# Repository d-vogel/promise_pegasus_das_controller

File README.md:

# Promise Pegasus DAS controller

The Promise Pegasus DAS is a thuderbolt 2 DAS enclosure.
| Front | Back |
|:-:|:-:|
|||

The goal here is to reverse engineer the backplane and replace the RAID controller with a SATA breakout board and microcontroller.

# Current Status
## reverse engineering
The reverse engineering of the backplane is done, for now described in [docs/backplane.md](docs/backplane.md).

## v0
The first PCB version is not present on the repo. The pinout for both the PCI connector and the ATX24 connector was completely wrong.
Is seems in the debugging process I damaged the CPLD controlling the LEDs, which is why v2 will add a ws2812 control pin.

## v1

This is the current version on the PCB. Pinouts are correct: 
- ✅ the pico is always on
- ✅ the front panel interfaces to the pico
- ✅ pico triggers the PSU
- ✅ CPLD control pins arrive where they should
- ✅ Disk power enable pins work
- ✅ sata works (tested with HDD1 only)
- ❌ ground fill missing, bodge wires were needed.

## v2 (TODO)
- add ws2812 control pin to pico
- add ground fill to the PCB
- add onboard temperature sensor

## v3 eInk front panel?
[waveshare 2.9 inch E-paper Module](https://www.waveshare.com/2.9inch-e-paper-module.htm)

# BOM:
- SATA: https://www.mouser.ch/ProductDetail/Adam-Tech/SATA-A-PL-VT-K-1
- PCI: https://www.mouser.ch/ProductDetail/Amphenol-FCI/10018783-10212TLF
- ATX24pin: https://www.mouser.fr/ProductDetail/TE-Connectivity/1-1775099-3?qs=28ld6GkVMjRzvehyCXdQkg%3D%3D

pio simulator: https://ice458.github.io/tools/pio_sim/index.html

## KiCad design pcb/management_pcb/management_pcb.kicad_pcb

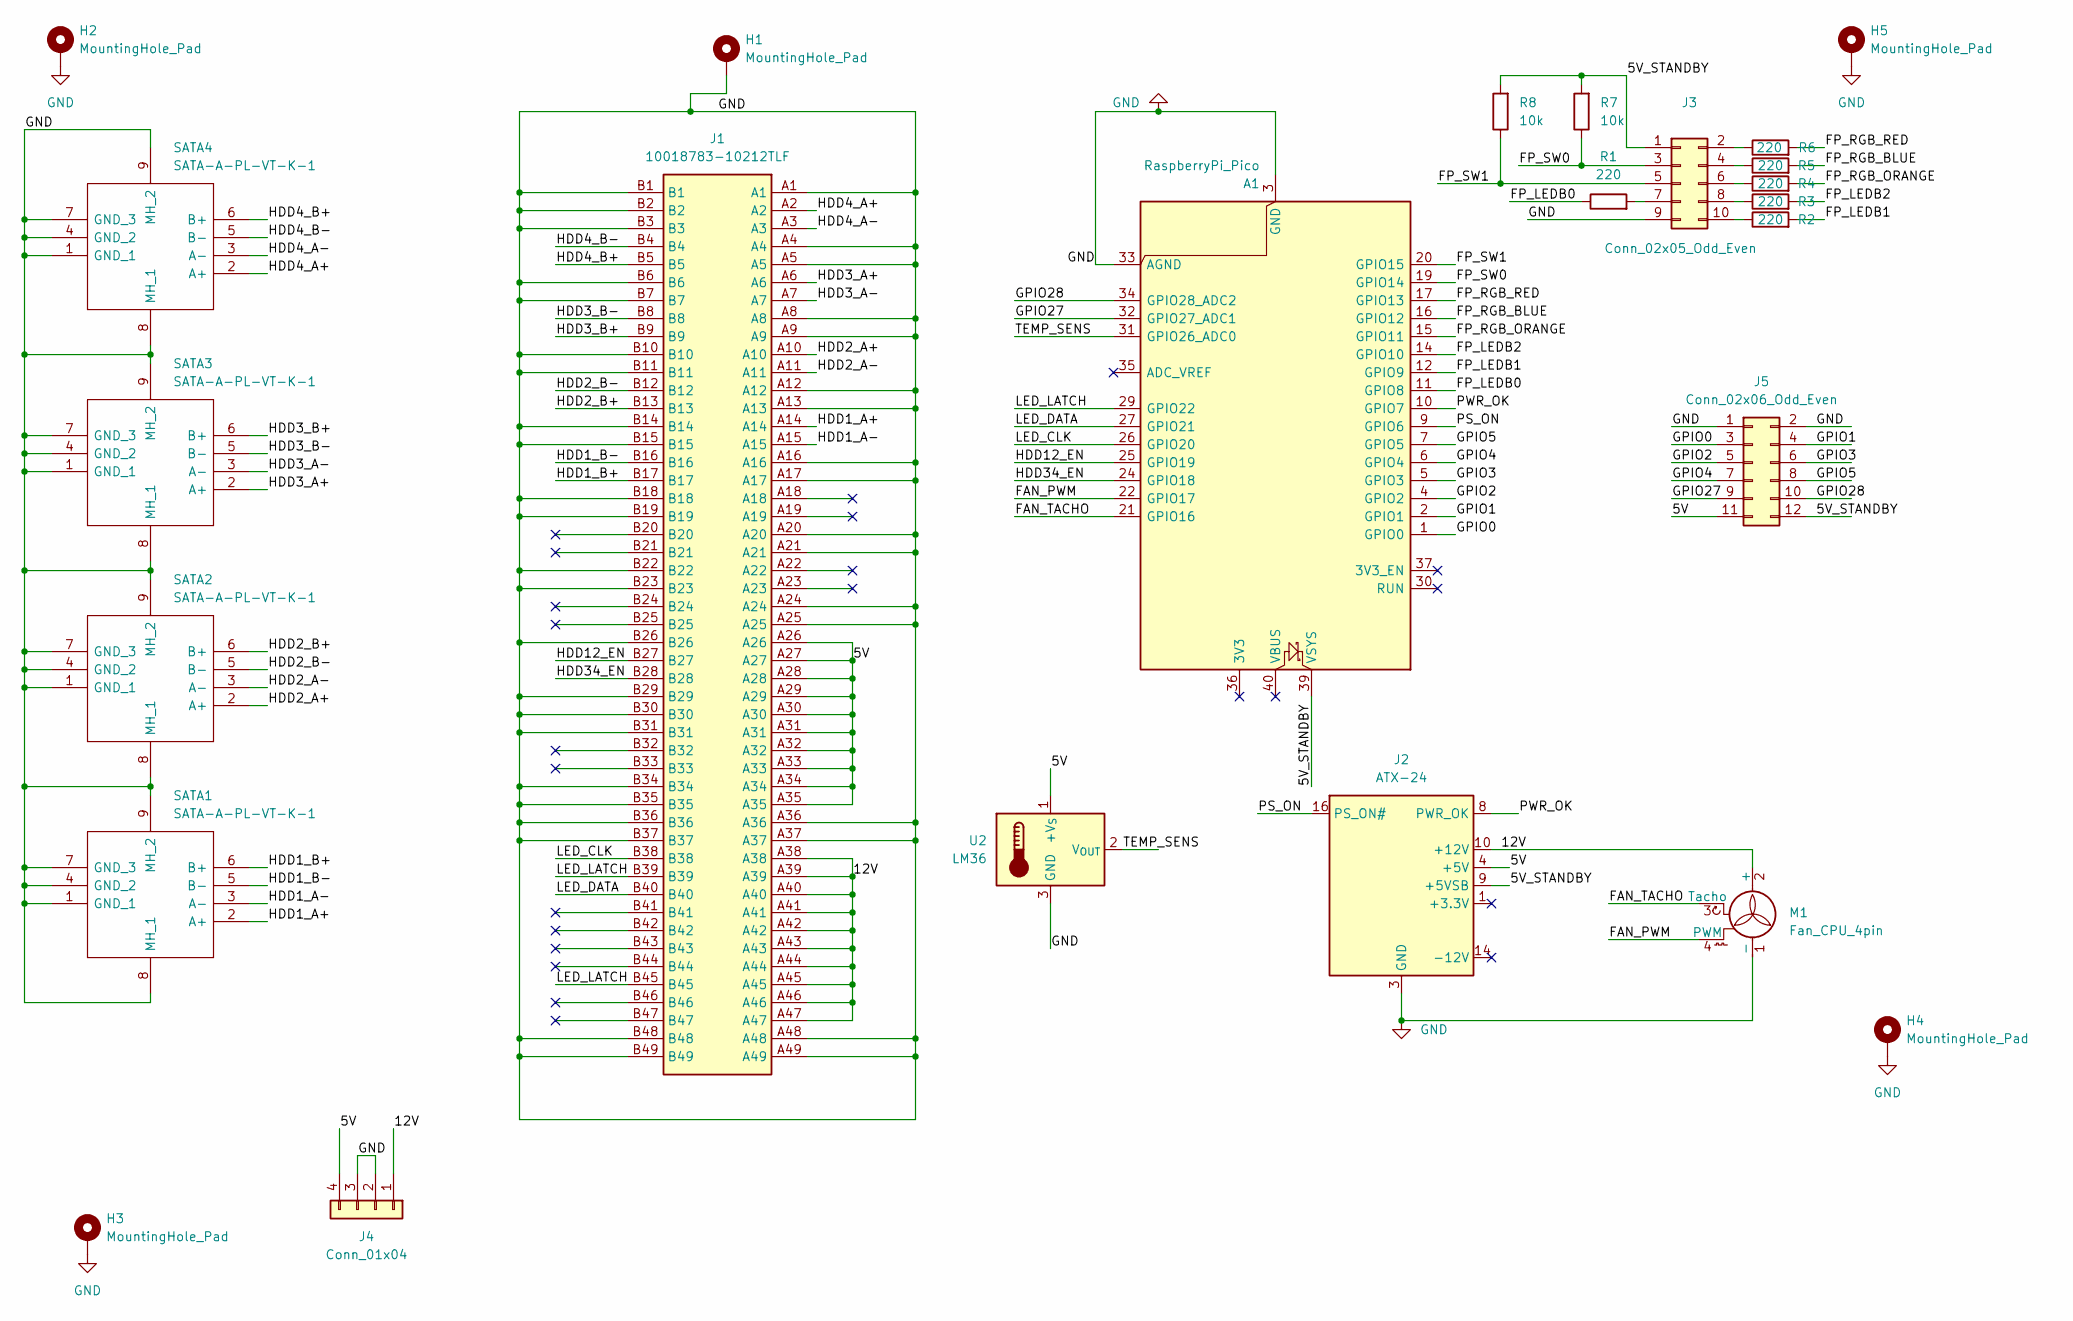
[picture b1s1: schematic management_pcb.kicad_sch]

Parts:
A1: RaspberryPi_Pico; RaspberryPi_Pico_Common_Unspecified
H1, H2, H3, H4, H5: MountingHole_Pad; MountingHole_4.3mm_M4_DIN965_Pad_TopBottom
J1: 10018783-10212TLF; 1001878310212TLF; Mouser Part Number 649-118783-10212TLF
J2: ATX-24; Molex_Mini-Fit_Jr_5566-24A_2x12_P4.20mm_Vertical
J3: Conn_02x05_Odd_Even; IDC_2x05_P2.00mm_Header
J4: Conn_01x04; SolderWire-0.75sqmm_1x04_P7mm_D1.25mm_OD3.5mm
J5: Conn_02x06_Odd_Even; PinHeader_2x06_P2.54mm_Vertical
M1: Fan_CPU_4pin; FanPinHeader_1x04_P2.54mm_Vertical
R1, R2, R3, R4, R5, R6: 220; R_0805_2012Metric
R7, R8: 10k; R_0805_2012Metric
SATA1, SATA2, SATA3, SATA4: SATA-A-PL-VT-K-1; SATAAPLVTK1; Manufacturer_Part_Number SATA-A-PL-VT-K-1
U2: LM36; TO-92_Inline

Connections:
/5V: J1.A26, J1.A27, J1.A28, J1.A29, J1.A30, J1.A31, J1.A32, J1.A33, J1.A34, J1.A35, J2.4 (+5V), J2.6 (+5V), J2.21 (+5V), J2.22 (+5V), J2.23 (+5V), J4.4, J5.11, U2.1 (+V_{S})
/5V_STANDBY: A1.39 (VSYS), J2.9 (+5VSB), J3.1, J5.12, R7.2, R8.2
/12V: J1.A38, J1.A39, J1.A40, J1.A41, J1.A42, J1.A43, J1.A44, J1.A45, J1.A46, J1.A47, J2.10 (+12V), J2.11 (+12V), J4.1, M1.2 (+)
/FAN_PWM: A1.22 (GPIO17), M1.4 (PWM)
/FAN_TACHO: A1.21 (GPIO16), M1.3 (Tacho)
/FP_LEDB0: A1.11 (GPIO8), R1.1
/FP_LEDB1: A1.12 (GPIO9), R2.2
/FP_LEDB2: A1.14 (GPIO10), R3.2
/FP_RGB_BLUE: A1.16 (GPIO12), R5.2
/FP_RGB_ORANGE: A1.15 (GPIO11), R4.2
/FP_RGB_RED: A1.17 (GPIO13), R6.2
/FP_SW0: A1.19 (GPIO14), J3.3, R7.1
/FP_SW1: A1.20 (GPIO15), J3.5, R8.1
/GPIO0: A1.1 (GPIO0), J5.3
/GPIO1: A1.2 (GPIO1), J5.4
/GPIO2: A1.4 (GPIO2), J5.5
/GPIO3: A1.5 (GPIO3), J5.6
/GPIO4: A1.6 (GPIO4), J5.7
/GPIO5: A1.7 (GPIO5), J5.8
/GPIO27: A1.32 (GPIO27_ADC1), J5.9
/GPIO28: A1.34 (GPIO28_ADC2), J5.10
/HDD1_A+: J1.A14, SATA1.2 (A+)
/HDD1_A-: J1.A15, SATA1.3 (A-)
/HDD1_B+: J1.B17, SATA1.6 (B+)
/HDD1_B-: J1.B16, SATA1.5 (B-)
/HDD2_A+: J1.A10, SATA2.2 (A+)
/HDD2_A-: J1.A11, SATA2.3 (A-)
/HDD2_B+: J1.B13, SATA2.6 (B+)
/HDD2_B-: J1.B12, SATA2.5 (B-)
/HDD3_A+: J1.A6, SATA3.2 (A+)
/HDD3_A-: J1.A7, SATA3.3 (A-)
/HDD3_B+: J1.B9, SATA3.6 (B+)
/HDD3_B-: J1.B8, SATA3.5 (B-)
/HDD4_A+: J1.A2, SATA4.2 (A+)
/HDD4_A-: J1.A3, SATA4.3 (A-)
/HDD4_B+: J1.B5, SATA4.6 (B+)
/HDD4_B-: J1.B4, SATA4.5 (B-)
/HDD12_EN: A1.25 (GPIO19), J1.B27
/HDD34_EN: A1.24 (GPIO18), J1.B28
/LED_CLK: A1.26 (GPIO20), J1.B38
/LED_DATA: A1.27 (GPIO21), J1.B40
/LED_LATCH: A1.29 (GPIO22), J1.B39, J1.B45
/PS_ON: A1.9 (GPIO6), J2.16 (PS_ON#)
/PWR_OK: A1.10 (GPIO7), J2.8 (PWR_OK)
/TEMP_SENS: A1.31 (GPIO26_ADC0), U2.2 (V_{OUT})
GND: A1.3 (GND), A1.8 (GND), A1.13 (GND), A1.18 (GND), A1.23 (GND), A1.28 (GND), A1.33 (AGND), A1.38 (GND), H1.1 (1_1), H2.1 (1_1), H3.1 (1_1), H4.1 (1_1), H5.1 (1_1), J1.A1, J1.A4, J1.A5, J1.A8, J1.A9, J1.A12, J1.A13, J1.A16, J1.A17, J1.A20, J1.A21, J1.A24, J1.A25, J1.A36, J1.A37, J1.A48, J1.A49, J1.B1, J1.B2, J1.B3, J1.B6, J1.B7, J1.B10, J1.B11, J1.B14, J1.B15, J1.B18, J1.B19, J1.B22, J1.B23, J1.B26, J1.B29, J1.B30, J1.B31, J1.B34, J1.B35, J1.B36, J1.B37, J1.B48, J1.B49, J2.3 (GND), J2.5 (GND), J2.7 (GND), J2.15 (GND), J2.17 (GND), J2.18 (GND), J2.19 (GND), J2.24 (GND), J3.9, J4.2, J4.3, J5.1, J5.2, M1.1 (-), SATA1.1 (GND_1), SATA1.4 (GND_2), SATA1.7 (GND_3), SATA1.8 (MH_1), SATA1.9 (MH_2), SATA2.1 (GND_1), SATA2.4 (GND_2), SATA2.7 (GND_3), SATA2.8 (MH_1), SATA2.9 (MH_2), SATA3.1 (GND_1), SATA3.4 (GND_2), SATA3.7 (GND_3), SATA3.8 (MH_1), SATA3.9 (MH_2), SATA4.1 (GND_1), SATA4.4 (GND_2), SATA4.7 (GND_3), SATA4.8 (MH_1), SATA4.9 (MH_2), U2.3 (GND)
unnamed: J3.2, R6.1
unnamed: J3.4, R5.1
unnamed: J3.6, R4.1
unnamed: J3.7, R1.2
unnamed: J3.8, R3.1
unnamed: J3.10, R2.1

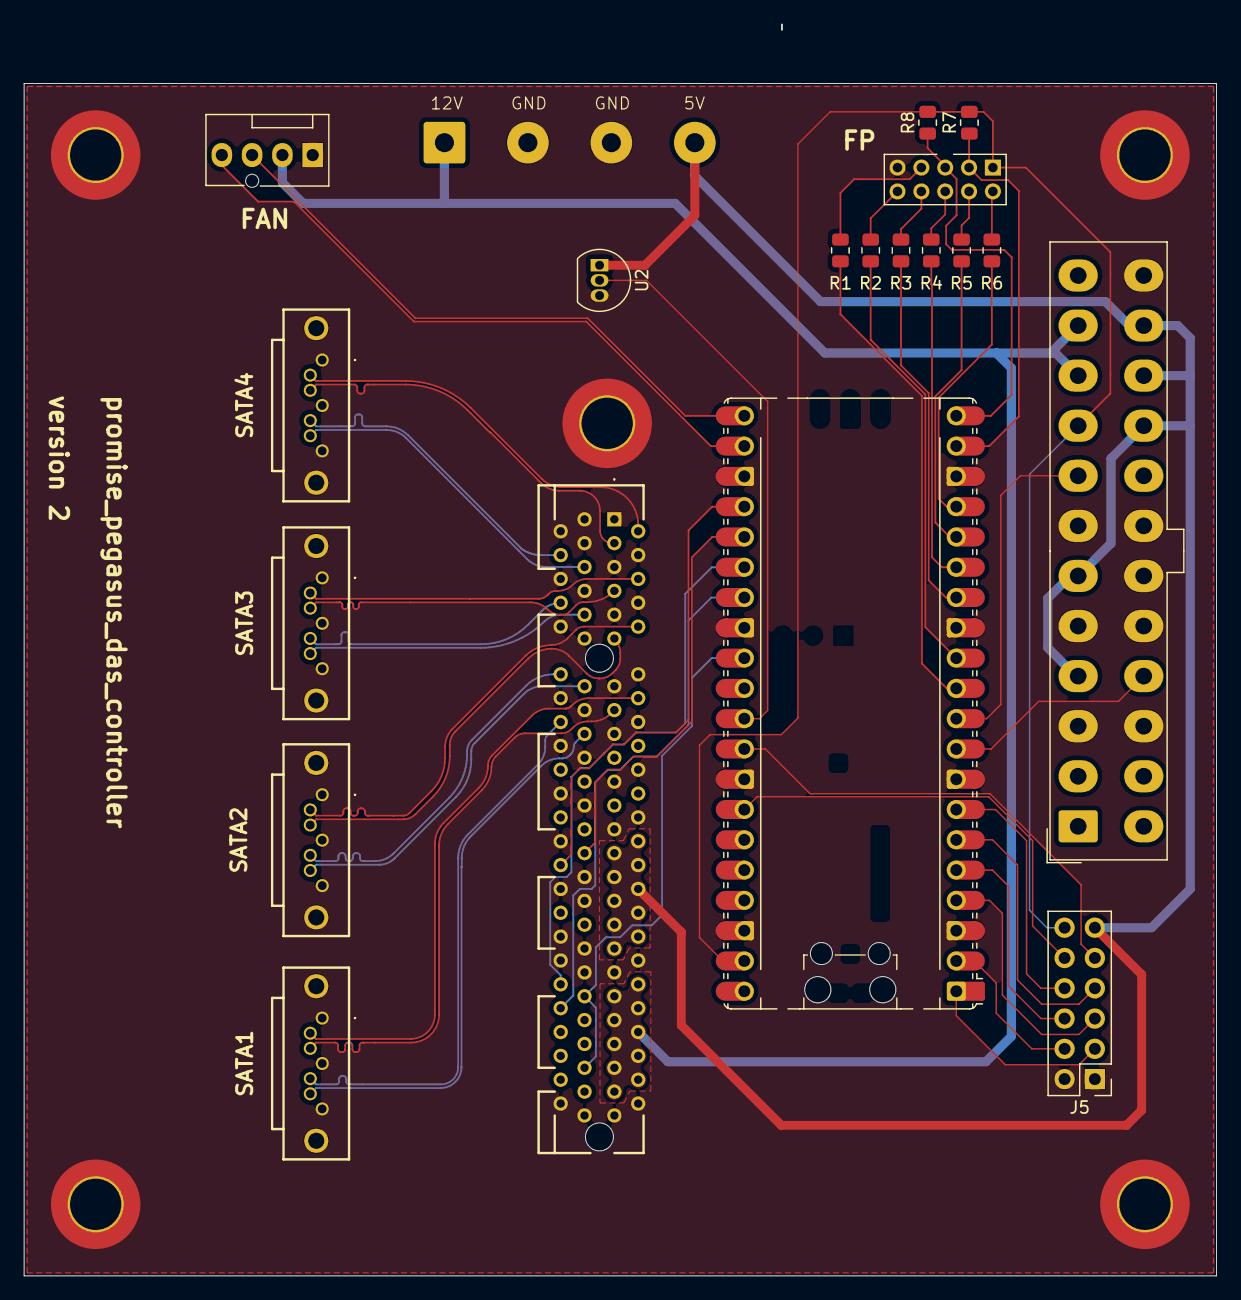
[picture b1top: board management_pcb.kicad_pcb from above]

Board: 2 copper layers, 100.0 x 105.0 mm, 25 parts (0 on the bottom side), 52 nets.

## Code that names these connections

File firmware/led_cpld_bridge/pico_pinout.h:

#ifndef PICO_PINOUT_H
#define PICO_PINOUT_H

#define GPIO0 0
#define GPIO1 1
#define GPIO2 2
#define GPIO3 3
#define GPIO4 4
#define GPIO5 5
#define PSU_ON 6
#define PSU_PWR_OK 7
#define FP_LEDB0 8
#define FP_LEDB1 9
#define FP_LEDB2 10
#define FP_RGB_ORANGE 11
#define FP_RGB_BLUE 12
#define FP_RGB_RED 13
#define FP_SW0 14
#define FP_SW1 15
#define FAN_TACHO 16
#define FAN_PWM 17
#define HDD34_EN 18
#define HDD12_EN 19
#define LED_CLK 20
#define LED_DATA 21
#define LED_LATCH 22

#define PICO_LED 25

#endif // PICO_PINOUT_H
